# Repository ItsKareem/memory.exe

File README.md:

# memory.exe
An RP2040 devboard that doubles as a flash drive

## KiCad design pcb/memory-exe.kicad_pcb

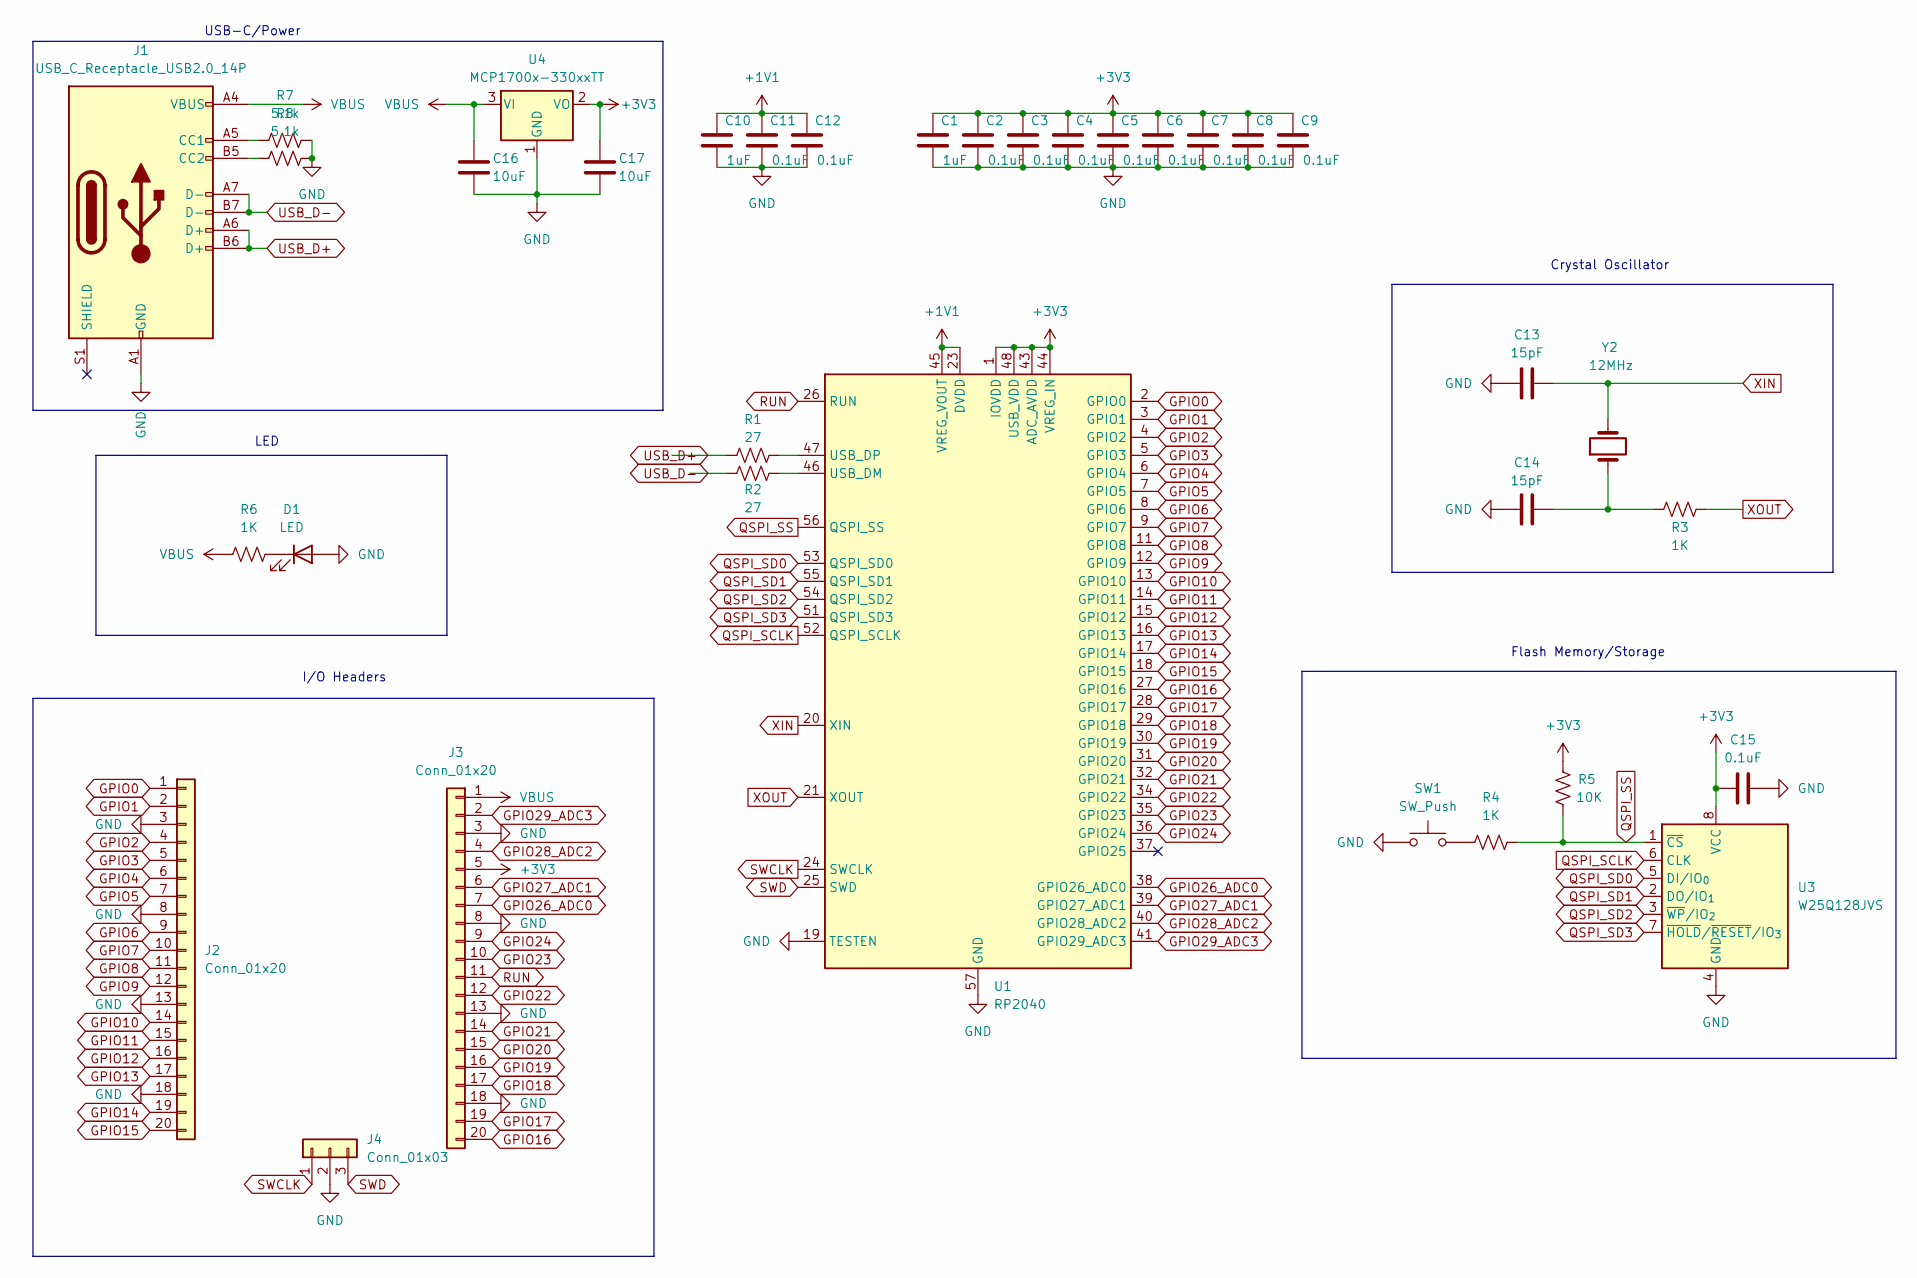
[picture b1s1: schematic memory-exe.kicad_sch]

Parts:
C1, C10: 1uF; C_0402_1005Metric
C2, C3, C4, C5, C6, C7, C8, C9, C11, C12, C15: 0.1uF; C_0402_1005Metric
C13, C14: 15pF; C_0402_1005Metric
C16, C17: 10uF; C_0201_0603Metric
D1: LED; LED-0603
J1: USB_C_Receptacle_USB2.0_14P; USB_C_Receptacle_HRO_TYPE-C-31-M-12
J2, J3: Conn_01x20; PinHeader_1x20_P2.54mm_Vertical
J4: Conn_01x03; PinHeader_1x03_P2.54mm_Vertical
R1, R2: 27; R_0402_1005Metric
R3, R4, R6: 1K; R_0402_1005Metric
R5: 10K; R_0402_1005Metric
R7, R8: 5.1k; R_0402_1005Metric
SW1: SW_Push; SW_Push_SPST_NO_Alps_SKRK
U1: RP2040; QFN-56-1EP_7x7mm_P0.4mm_EP3.2x3.2mm
U3: W25Q128JVS; Winbond_USON-8-1EP_3x2mm_P0.5mm_EP0.2x1.6mm
U4: MCP1700x-330xxTT; SOT-23
Y2: 12MHz; Crystal_SMD_3225-4Pin_3.2x2.5mm

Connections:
+1V1: C10.1, C11.1, C12.1, U1.23 (DVDD), U1.45 (VREG_VOUT), U1.50 (DVDD)
+3V3: C1.1, C2.1, C3.1, C4.1, C5.1, C6.1, C7.1, C8.1, C9.1, C15.1, C17.1, J3.5, R5.1, U1.1 (IOVDD), U1.10 (IOVDD), U1.22 (IOVDD), U1.33 (IOVDD), U1.42 (IOVDD), U1.43 (ADC_AVDD), U1.44 (VREG_IN), U1.48 (USB_VDD), U1.49 (IOVDD), U3.8 (VCC), U4.2 (VO)
GND: C1.2, C2.2, C3.2, C4.2, C5.2, C6.2, C7.2, C8.2, C9.2, C10.2, C11.2, C12.2, C13.2, C14.2, C15.2, C16.2, C17.2, D1.2 (A), J1.A1 (GND), J1.A12 (GND), J1.B1 (GND), J1.B12 (GND), J2.3, J2.8, J2.13, J2.18, J3.3, J3.8, J3.13, J3.18, J4.2, R7.2, R8.1, SW1.1, U1.19 (TESTEN), U1.57 (GND), U3.4 (GND), U4.1 (GND)
GPIO0: J2.1, U1.2 (GPIO0)
GPIO1: J2.2, U1.3 (GPIO1)
GPIO2: J2.4, U1.4 (GPIO2)
GPIO3: J2.5, U1.5 (GPIO3)
GPIO4: J2.6, U1.6 (GPIO4)
GPIO5: J2.7, U1.7 (GPIO5)
GPIO6: J2.9, U1.8 (GPIO6)
GPIO7: J2.10, U1.9 (GPIO7)
GPIO8: J2.11, U1.11 (GPIO8)
GPIO9: J2.12, U1.12 (GPIO9)
GPIO10: J2.14, U1.13 (GPIO10)
GPIO11: J2.15, U1.14 (GPIO11)
GPIO12: J2.16, U1.15 (GPIO12)
GPIO13: J2.17, U1.16 (GPIO13)
GPIO14: J2.19, U1.17 (GPIO14)
GPIO15: J2.20, U1.18 (GPIO15)
GPIO16: J3.20, U1.27 (GPIO16)
GPIO17: J3.19, U1.28 (GPIO17)
GPIO18: J3.17, U1.29 (GPIO18)
GPIO19: J3.16, U1.30 (GPIO19)
GPIO20: J3.15, U1.31 (GPIO20)
GPIO21: J3.14, U1.32 (GPIO21)
GPIO22: J3.12, U1.34 (GPIO22)
GPIO23: J3.10, U1.35 (GPIO23)
GPIO24: J3.9, U1.36 (GPIO24)
GPIO26_ADC0: J3.7, U1.38 (GPIO26_ADC0)
GPIO27_ADC1: J3.6, U1.39 (GPIO27_ADC1)
GPIO28_ADC2: J3.4, U1.40 (GPIO28_ADC2)
GPIO29_ADC3: J3.2, U1.41 (GPIO29_ADC3)
unnamed: C14.1, R3.2, Y2.1
unnamed: D1.1 (K), R6.2
unnamed: J1.A5 (CC1), R7.1
unnamed: J1.B5 (CC2), R8.2
unnamed: R4.1, SW1.2
unnamed: R2.2, U1.46 (USB_DM)
unnamed: R1.2, U1.47 (USB_DP)
QSPI_SCLK: U1.52 (QSPI_SCLK), U3.6 (CLK)
QSPI_SD0: U1.53 (QSPI_SD0), U3.5 (DI/IO_{0})
QSPI_SD1: U1.55 (QSPI_SD1), U3.2 (DO/IO_{1})
QSPI_SD2: U1.54 (QSPI_SD2), U3.3 (~WP/IO_{2})
QSPI_SD3: U1.51 (QSPI_SD3), U3.7 (~HOLD/~RESET/IO_{3})
QSPI_SS: R4.2, R5.2, U1.56 (QSPI_SS), U3.1 (~CS)
RUN: J3.11, U1.26 (RUN)
SWCLK: J4.1, U1.24 (SWCLK)
SWD: J4.3, U1.25 (SWD)
USB_D+: J1.A6 (D+), J1.B6 (D+), R1.1
USB_D-: J1.A7 (D-), J1.B7 (D-), R2.1
VBUS: C16.1, J1.A4 (VBUS), J1.A9 (VBUS), J1.B4 (VBUS), J1.B9 (VBUS), J3.1, R6.1, U4.3 (VI)
XIN: C13.1, U1.20 (XIN), Y2.2
XOUT: R3.1, U1.21 (XOUT)

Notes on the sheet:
Flash Memory/Storage
USB-C/Power
Crystal Oscillator
LED
I/O Headers

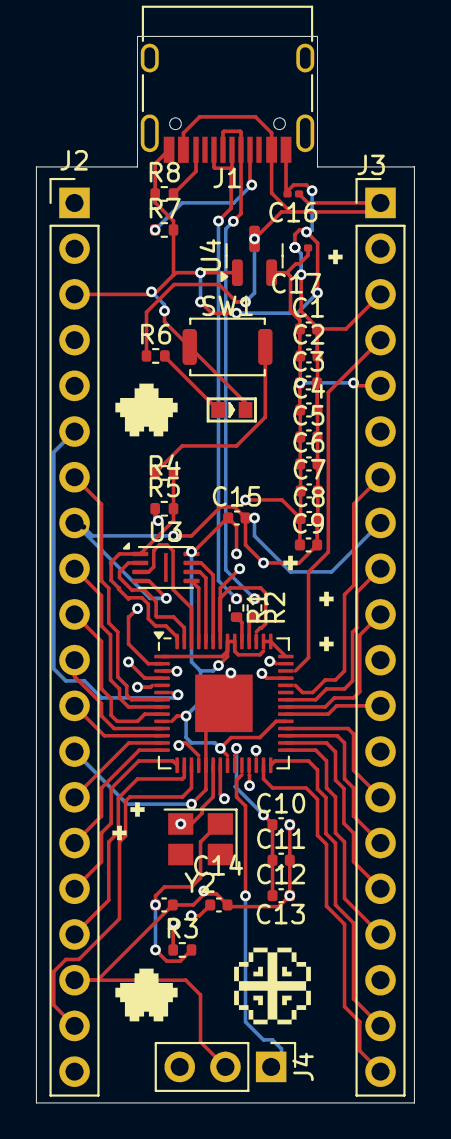
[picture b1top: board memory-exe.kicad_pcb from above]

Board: 4 copper layers, 21.0 x 59.2 mm, 35 parts (0 on the bottom side), 53 nets.

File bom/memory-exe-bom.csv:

"Reference","Qty","Value","DNP","Exclude from BOM","Exclude from Board","Footprint","Datasheet"
"C1,C10","2","1uF","","","","Capacitor_SMD:C_0402_1005Metric","~"
"C2,C3,C4,C5,C6,C7,C8,C9,C11,C12,C15","11","0.1uF","","","","Capacitor_SMD:C_0402_1005Metric","~"
"C13,C14","2","15pF","","","","Capacitor_SMD:C_0402_1005Metric","~"
"C16,C17","2","10uF","","","","Capacitor_SMD:C_0201_0603Metric","~"
"D1","1","LED","","","","OPL_Optoelectronics:LED-0603","~"
"J1","1","USB_C_Receptacle_USB2.0_14P","","","","Connector_USB:USB_C_Receptacle_HRO_TYPE-C-31-M-12","https://www.usb.org/sites/default/files/documents/usb_type-c.zip"
"J2,J3","2","Conn_01x20","","","","Connector_PinHeader_2.54mm:PinHeader_1x20_P2.54mm_Vertical","~"
"J4","1","Conn_01x03","","","","Connector_PinHeader_2.54mm:PinHeader_1x03_P2.54mm_Vertical","~"
"R1,R2","2","27","","","","Resistor_SMD:R_0402_1005Metric","~"
"R3,R4,R6","3","1K","","","","Resistor_SMD:R_0402_1005Metric","~"
"R5","1","10K","","","","Resistor_SMD:R_0402_1005Metric","~"
"R7,R8","2","5.1k","","","","Resistor_SMD:R_0402_1005Metric","~"
"SW1","1","SW_Push","","","","Button_Switch_SMD:SW_Push_SPST_NO_Alps_SKRK","~"
"U1","1","RP2040","","","","Package_DFN_QFN:QFN-56-1EP_7x7mm_P0.4mm_EP3.2x3.2mm","https://datasheets.raspberrypi.com/rp2040/rp2040-datasheet.pdf"
"U3","1","W25Q128JVS","","","","Package_SON:Winbond_USON-8-1EP_3x2mm_P0.5mm_EP0.2x1.6mm","https://www.winbond.com/resource-files/w25q128jv_dtr%20revc%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"
"U4","1","MCP1700x-330xxTT","","","","Package_TO_SOT_SMD:SOT-23","http://ww1.microchip.com/downloads/en/DeviceDoc/20001826D.pdf"
"Y2","1","12MHz","","","","Crystal:Crystal_SMD_3225-4Pin_3.2x2.5mm","~"

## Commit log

2026-06-21 Setup
2026-06-21 zine page and kicad files
2026-06-21 added bom and add a ladybug to the designs :3
2026-06-21 Made da README
    Updated the README to reflect changes from 'star-blinky' to 'memory.exe', including new features and descriptions.
2026-06-21 added a bg color of the schematic so it's actually visible bruh
2026-06-21 tweaked README
    Updated the title in the README to clarify the product description.
